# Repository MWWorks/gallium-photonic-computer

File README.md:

# Gallium Photonic Computer

A few files that folks have requested for the build of my Gallium Photonic Computer (!)

More details of the project:

* [On my site/blog](https://mwworks.uk/project/gallium-photonic-computer)
* Some [work in progress pics on Imgur](https://imgur.com/gallery/gallium-photonic-computer-led-supercomputer-5IYMQFF)
* Also see the [inspiration video by Big Clive](https://www.youtube.com/watch?v=7f8jgvvJe-Q)

Shared here are:

* The KiCad files for the PCB
* STLs and Freecad files for the baffles

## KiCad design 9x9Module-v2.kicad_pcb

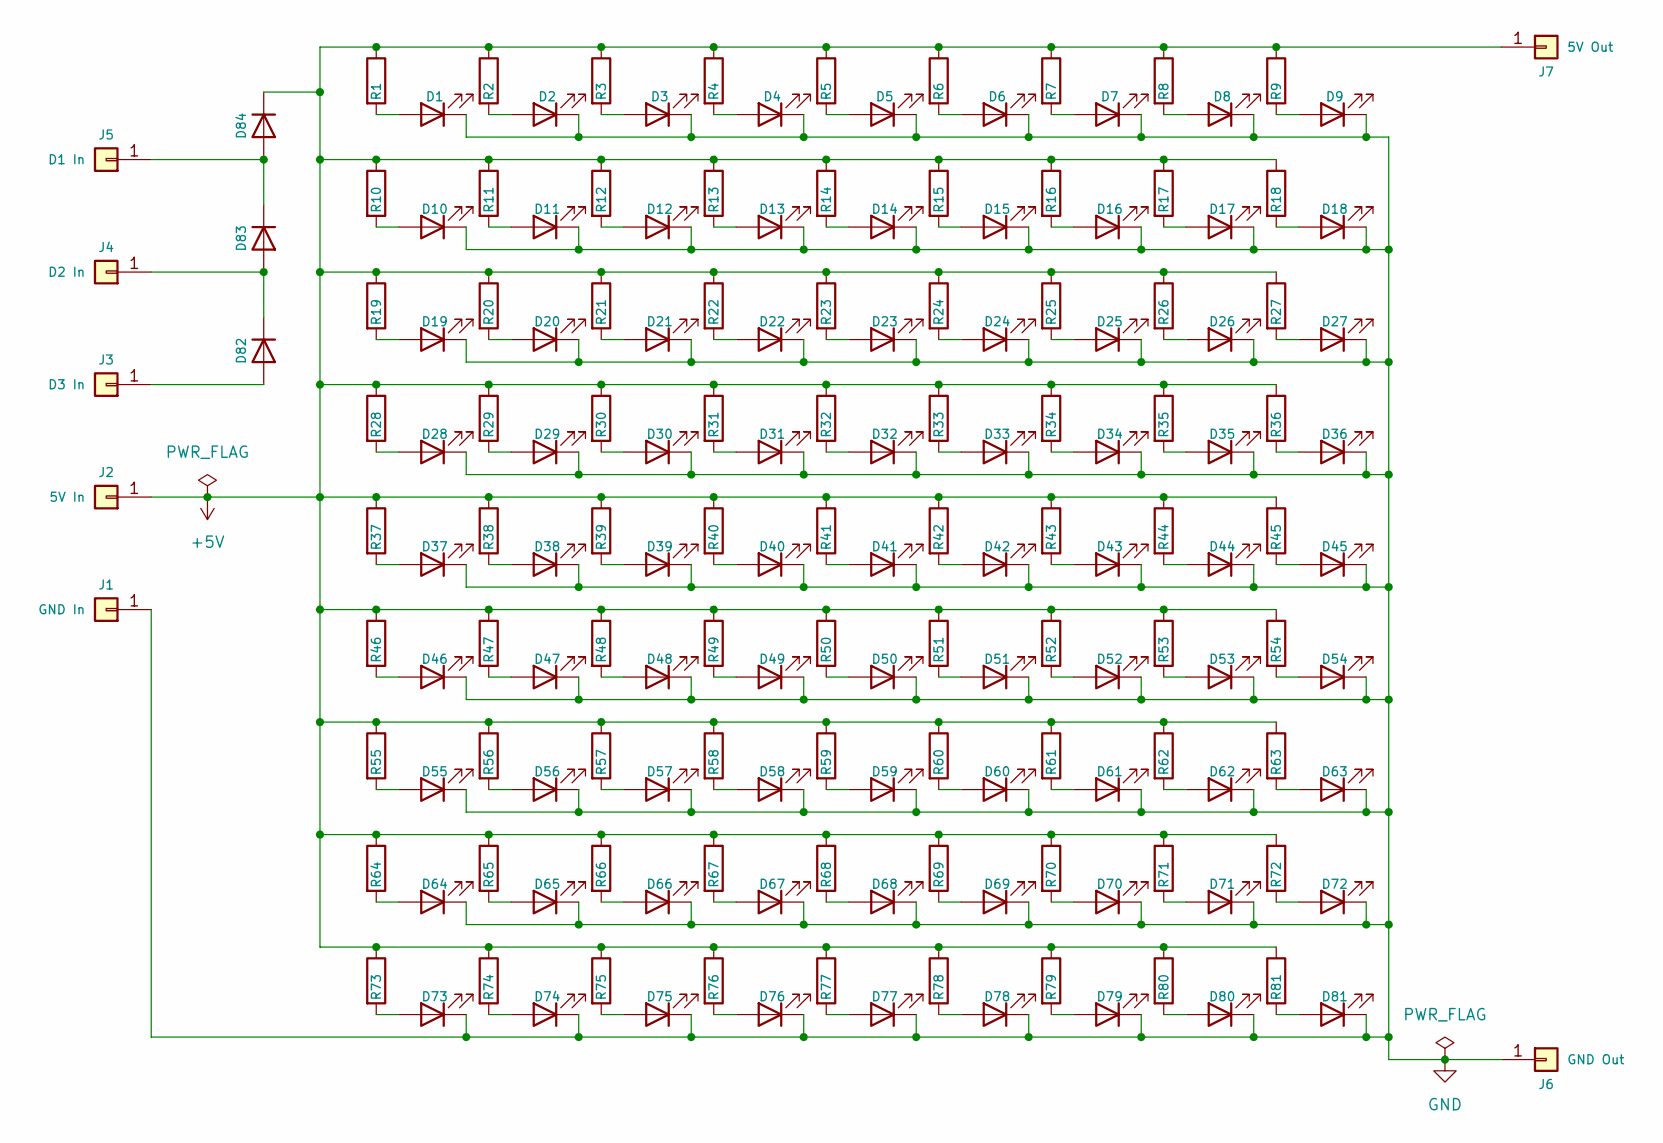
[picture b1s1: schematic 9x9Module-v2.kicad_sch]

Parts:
D1, D2, D3, D4, D5, D6, D7, D8, D9, D10, D11, D12, D13, D14, D15, D16, D17, D18, D19, D20, D21, D22, D23, D24, D25, D26, D27, D28, D29, D30, D31, D32, D33, D34, D35, D36, D37, D38, D39, D40, D41, D42, D43, D44, D45, D46, D47, D48, D49, D50, D51, D52, D53, D54, D55, D56, D57, D58, D59, D60, D61, D62, D63, D64, D65, D66, D67, D68, D69, D70, D71, D72, D73, D74, D75, D76, D77, D78, D79, D80, D81: LED; LED_D5.0mm
D82, D83, D84: US2MA; D_SMA; LCSC C18905
J1: GND In; TestPoint_Pad_D4.0mm
J2: 5V In; TestPoint_Pad_D4.0mm
J3: D3 In; TestPoint_Pad_D4.0mm
J4: D2 In; TestPoint_Pad_D4.0mm
J5: D1 In; TestPoint_Pad_D4.0mm
J6: GND Out; TestPoint_Pad_D4.0mm
J7: 5V Out; TestPoint_Pad_D4.0mm
R1, R2, R3, R4, R5, R6, R7, R8, R9, R10, R11, R12, R13, R14, R15, R16, R17, R18, R19, R20, R21, R22, R23, R24, R25, R26, R27, R28, R29, R30, R31, R32, R33, R34, R35, R36, R37, R38, R39, R40, R41, R42, R43, R44, R45, R46, R47, R48, R49, R50, R51, R52, R53, R54, R55, R56, R57, R58, R59, R60, R61, R62, R63, R64, R65, R66, R67, R68, R69, R70, R71, R72, R73, R74, R75, R76, R77, R78, R79, R80, R81: 470R; R_0805_2012Metric; LCSC C17710

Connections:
+5V: D84.1 (K), J2.1, J7.1, R1.1, R2.1, R3.1, R4.1, R5.1, R6.1, R7.1, R8.1, R9.1, R10.1, R11.1, R12.1, R13.1, R14.1, R15.1, R16.1, R17.1, R18.1, R19.1, R20.1, R21.1, R22.1, R23.1, R24.1, R25.1, R26.1, R27.1, R28.1, R29.1, R30.1, R31.1, R32.1, R33.1, R34.1, R35.1, R36.1, R37.1, R38.1, R39.1, R40.1, R41.1, R42.1, R43.1, R44.1, R45.1, R46.1, R47.1, R48.1, R49.1, R50.1, R51.1, R52.1, R53.1, R54.1, R55.1, R56.1, R57.1, R58.1, R59.1, R60.1, R61.1, R62.1, R63.1, R64.1, R65.1, R66.1, R67.1, R68.1, R69.1, R70.1, R71.1, R72.1, R73.1, R74.1, R75.1, R76.1, R77.1, R78.1, R79.1, R80.1, R81.1
GND: D1.1 (K), D2.1 (K), D3.1 (K), D4.1 (K), D5.1 (K), D6.1 (K), D7.1 (K), D8.1 (K), D9.1 (K), D10.1 (K), D11.1 (K), D12.1 (K), D13.1 (K), D14.1 (K), D15.1 (K), D16.1 (K), D17.1 (K), D18.1 (K), D19.1 (K), D20.1 (K), D21.1 (K), D22.1 (K), D23.1 (K), D24.1 (K), D25.1 (K), D26.1 (K), D27.1 (K), D28.1 (K), D29.1 (K), D30.1 (K), D31.1 (K), D32.1 (K), D33.1 (K), D34.1 (K), D35.1 (K), D36.1 (K), D37.1 (K), D38.1 (K), D39.1 (K), D40.1 (K), D41.1 (K), D42.1 (K), D43.1 (K), D44.1 (K), D45.1 (K), D46.1 (K), D47.1 (K), D48.1 (K), D49.1 (K), D50.1 (K), D51.1 (K), D52.1 (K), D53.1 (K), D54.1 (K), D55.1 (K), D56.1 (K), D57.1 (K), D58.1 (K), D59.1 (K), D60.1 (K), D61.1 (K), D62.1 (K), D63.1 (K), D64.1 (K), D65.1 (K), D66.1 (K), D67.1 (K), D68.1 (K), D69.1 (K), D70.1 (K), D71.1 (K), D72.1 (K), D73.1 (K), D74.1 (K), D75.1 (K), D76.1 (K), D77.1 (K), D78.1 (K), D79.1 (K), D80.1 (K), D81.1 (K), J1.1, J6.1
unnamed: D1.2 (A), R1.2
unnamed: D2.2 (A), R2.2
unnamed: D3.2 (A), R3.2
unnamed: D4.2 (A), R4.2
unnamed: D5.2 (A), R5.2
unnamed: D6.2 (A), R6.2
unnamed: D7.2 (A), R7.2
unnamed: D8.2 (A), R8.2
unnamed: D9.2 (A), R9.2
unnamed: D10.2 (A), R10.2
unnamed: D11.2 (A), R11.2
unnamed: D12.2 (A), R12.2
unnamed: D13.2 (A), R13.2
unnamed: D14.2 (A), R14.2
unnamed: D15.2 (A), R15.2
unnamed: D16.2 (A), R16.2
unnamed: D17.2 (A), R17.2
unnamed: D18.2 (A), R18.2
unnamed: D19.2 (A), R19.2
unnamed: D20.2 (A), R20.2
unnamed: D21.2 (A), R21.2
unnamed: D22.2 (A), R22.2
unnamed: D23.2 (A), R23.2
unnamed: D24.2 (A), R24.2
unnamed: D25.2 (A), R25.2
unnamed: D26.2 (A), R26.2
unnamed: D27.2 (A), R27.2
unnamed: D28.2 (A), R28.2
unnamed: D29.2 (A), R29.2
unnamed: D30.2 (A), R30.2
unnamed: D31.2 (A), R31.2
unnamed: D32.2 (A), R32.2
unnamed: D33.2 (A), R33.2
unnamed: D34.2 (A), R34.2
unnamed: D35.2 (A), R35.2
unnamed: D36.2 (A), R36.2
unnamed: D37.2 (A), R37.2
unnamed: D38.2 (A), R38.2
unnamed: D39.2 (A), R39.2
unnamed: D40.2 (A), R40.2
unnamed: D41.2 (A), R41.2
unnamed: D42.2 (A), R42.2
unnamed: D43.2 (A), R43.2
unnamed: D44.2 (A), R44.2
unnamed: D45.2 (A), R45.2
unnamed: D46.2 (A), R46.2
unnamed: D47.2 (A), R47.2
unnamed: D48.2 (A), R48.2
unnamed: D49.2 (A), R49.2
unnamed: D50.2 (A), R50.2
unnamed: D51.2 (A), R51.2
unnamed: D52.2 (A), R52.2
unnamed: D53.2 (A), R53.2
unnamed: D54.2 (A), R54.2
unnamed: D55.2 (A), R55.2
unnamed: D56.2 (A), R56.2
unnamed: D57.2 (A), R57.2
unnamed: D58.2 (A), R58.2
unnamed: D59.2 (A), R59.2
unnamed: D60.2 (A), R60.2
unnamed: D61.2 (A), R61.2
unnamed: D62.2 (A), R62.2
unnamed: D63.2 (A), R63.2
unnamed: D64.2 (A), R64.2
unnamed: D65.2 (A), R65.2
unnamed: D66.2 (A), R66.2
unnamed: D67.2 (A), R67.2
unnamed: D68.2 (A), R68.2
unnamed: D69.2 (A), R69.2
unnamed: D70.2 (A), R70.2
unnamed: D71.2 (A), R71.2
unnamed: D72.2 (A), R72.2
unnamed: D73.2 (A), R73.2
unnamed: D74.2 (A), R74.2
unnamed: D75.2 (A), R75.2
unnamed: D76.2 (A), R76.2
unnamed: D77.2 (A), R77.2
unnamed: D78.2 (A), R78.2
unnamed: D79.2 (A), R79.2
unnamed: D80.2 (A), R80.2
unnamed: D81.2 (A), R81.2
unnamed: D82.2 (A), J3.1
unnamed: D82.1 (K), D83.2 (A), J4.1
unnamed: D83.1 (K), D84.2 (A), J5.1

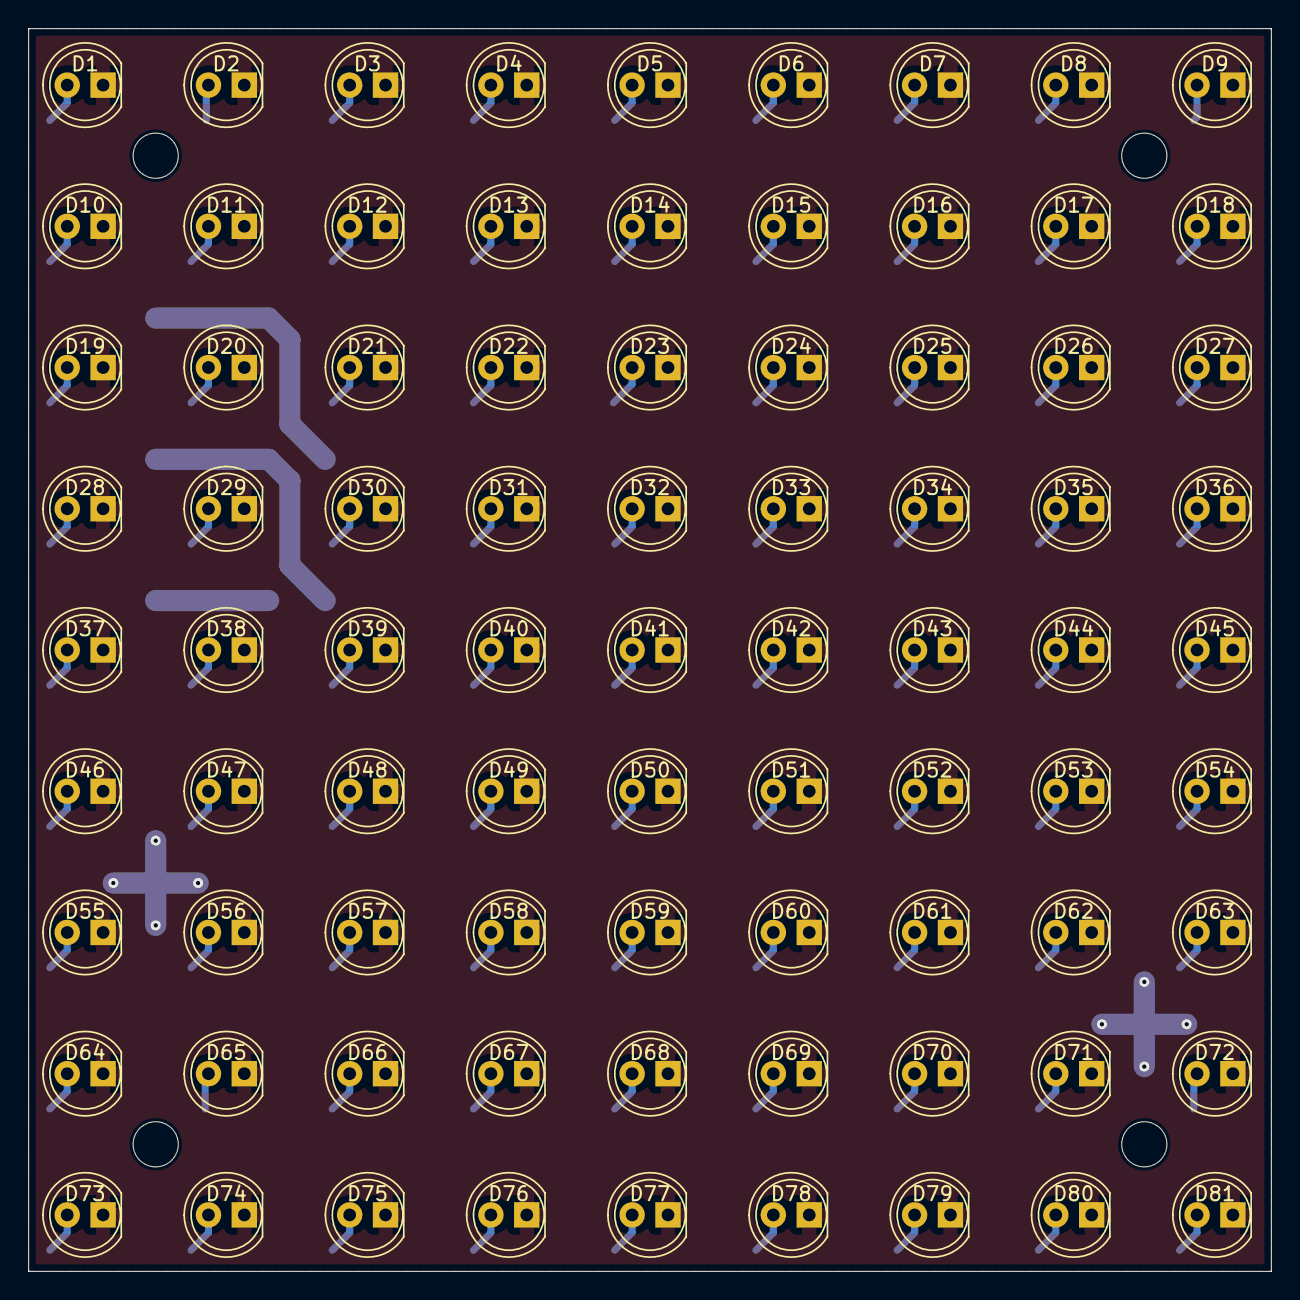
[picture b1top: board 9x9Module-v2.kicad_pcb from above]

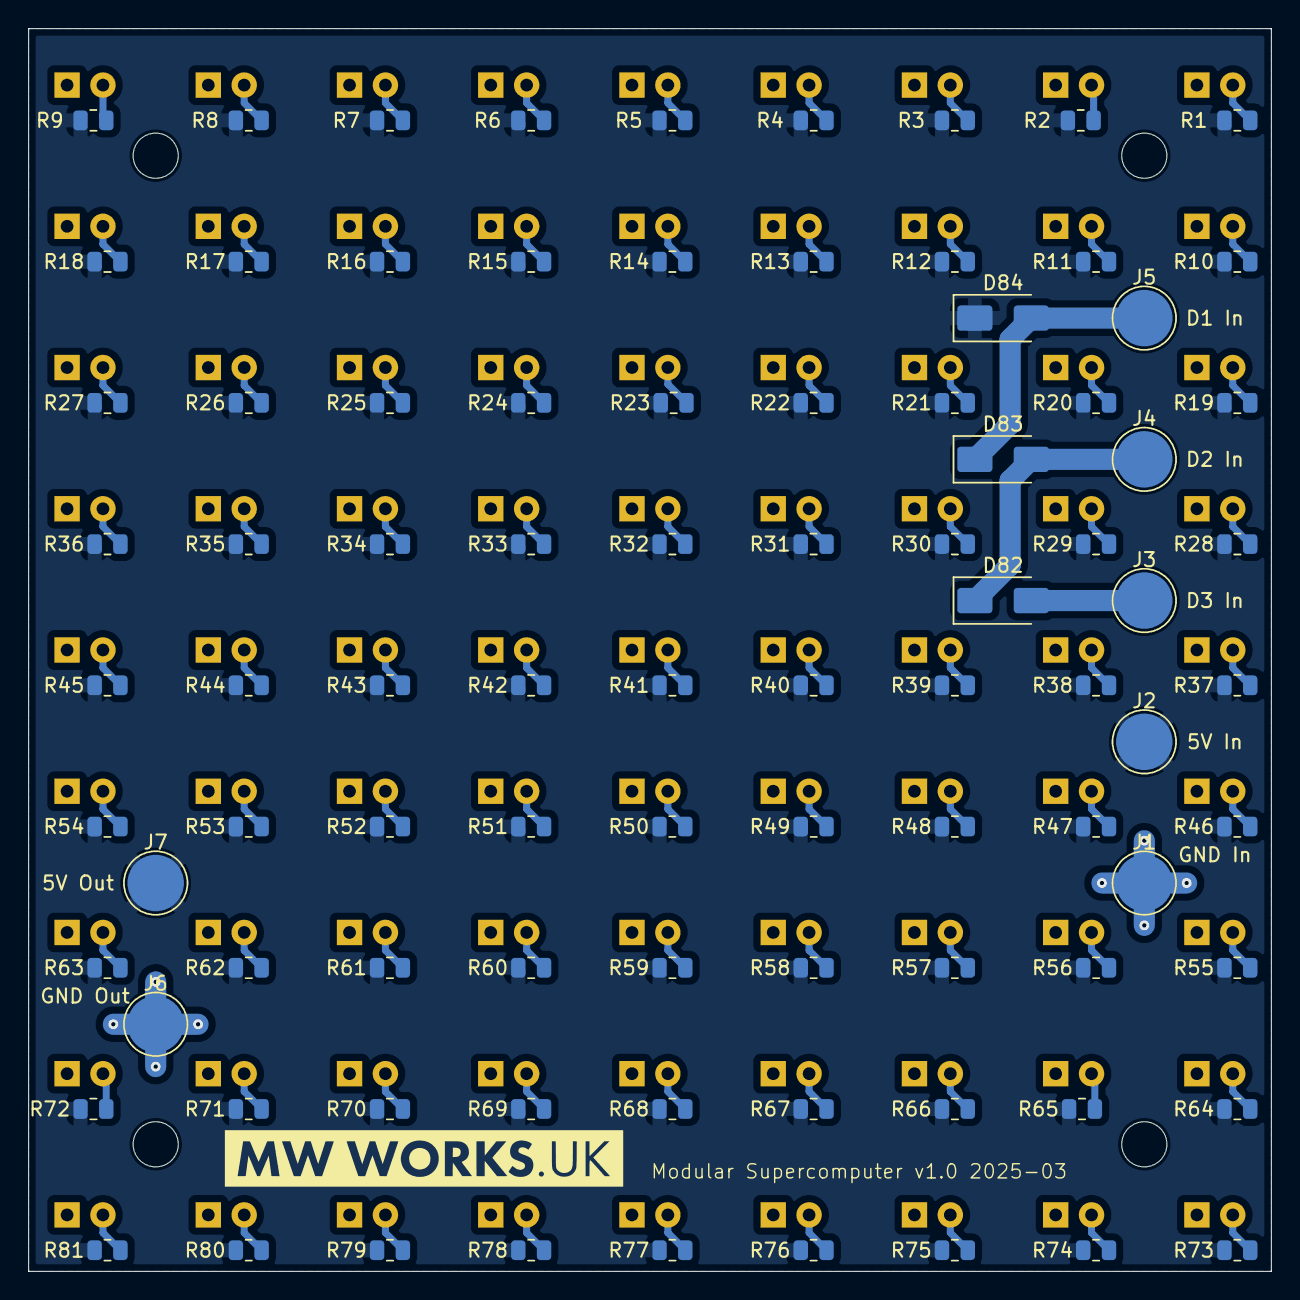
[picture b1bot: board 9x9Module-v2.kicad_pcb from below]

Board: 2 copper layers, 88.0 x 88.0 mm, 172 parts (91 on the bottom side), 86 nets.
